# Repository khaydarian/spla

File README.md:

# SPLA: Super Nintendo PPU Logic Analyzer

The 1990-era Super Nintendo Entertainment System is a venerable gaming console,
and although its hardware is aging and hard to come by, it has long had
well-establish software emulators, preserving gaming history for generations to
come.

However, while most of the SNES hardware has been effectively
reverse-engineered by writing test programs for the CPU (sometimes taking
advantage of undocumented behavior to figure out details), one remaining
component of the console has resisted complete analysis: the "Picture
Processing Unit" chips, `PPU-1` and `PPU-2`.

The PPU chips are together responsible for managing the sprites, backgrounds,
and palettes for each frame of a game's video output, and produce the analog
scanline signal in realtime, which then appears on the
player's TV.  However, the output video signals (and video ram bus) are
entirely inaccessible to SNES CPU, thus making analysis of the exact timing
details of these chips difficult or impossible.

A very few games for the SNES (particularly *Air Strike Patrol*) use the SNES
video hardware in unexpected ways, which depend on the detailed timing of the
PPU chips during scanline rendering.  This makes accurately emulating these
games' graphics difficult -- emulator developers have to manually compare
emulator output with what the game actually shows on the screen, and try to
guess how the PPU evaluates these unusual configurations.  Without complete
understanding of the chips operation, this process degenerates into a
frustruating game of whack-a-mole.

To be confident that we have faithfully reproduced the entire SNES, we need to
characterize all the PPU outputs at the level of individual clock cycles, and
rigorously compare the behavior of a software emulator to that of the actual,
physical chips.

This project is intended to design a breakout circuit board, integrating the
SNES PPU chips from a real vintage SNES console, combined with surrounding
modern hardware, to effectively form a >100-pin-wide digital logic analyzer,
combined with single-frame analog video capture system.  With this board built,
and sufficient supporting software written, it should be possible to
experimentally characterize the entire operation of the PPU chips, thus
producing a completely cycle-accurate emulation of the SNES video hardware.

</img>

## Current Status

* Design complete.
* Schematic complete.
* PCB layout complete.
* Schematic and PCB review complete (enough).
* Lab setup essentially complete.
* Bringup started.
  * Power bringup complete.
  * USB / FTDI bringup complete.
  * FPGA bringup complete.
  * Level shifter bringup complete.
  * SNES bringup complete.
  * Analog bringup pending.
* Software development in progress.
  * Early bringup and testing software complete.
* RTL development in progress.
  * All bringup images complete.
  * Low-speed driver image in progress.
  * High-speed driver image pending.

## Design components

* The USB interface to a host PC is based on an FTDI `FT2232H` chip, which can
  drive up to 60MBps (USB 2.0 "Full Speed" maximum throughput).
* A Lattice `ECP5` FPGA, which forms the central brains of the board.
* Both SNES `PPU` chips, and their corresponding video SRAM chips (which are
  standard 32KiB 8-bit SRAM chips, but are old enough that they're hard to
  source).
* A whole bunch of 3.3V / 5V level shifter chips (`74LVC8T245`), as the SNES
  chips are 5V TTL, but almost everything modern is 3.3V at most.
* Three `ADC1173` high-speed 8-bit analog-to-digital converter chips, to
  capture the analog RGB signal output and convert it back to digital for
  analysis. This also requires a handful (5) of `LMH6611` opamps to drive the
  ADC inputs and establish reliable references.

## References

* [Original post that inspired this project](https://byuu.org/articles/edge-of-emulation)
* [Ars Technica Article](https://arstechnica.com/gaming/2020/04/how-snes-emulators-got-a-few-pixels-from-complete-perfection/)

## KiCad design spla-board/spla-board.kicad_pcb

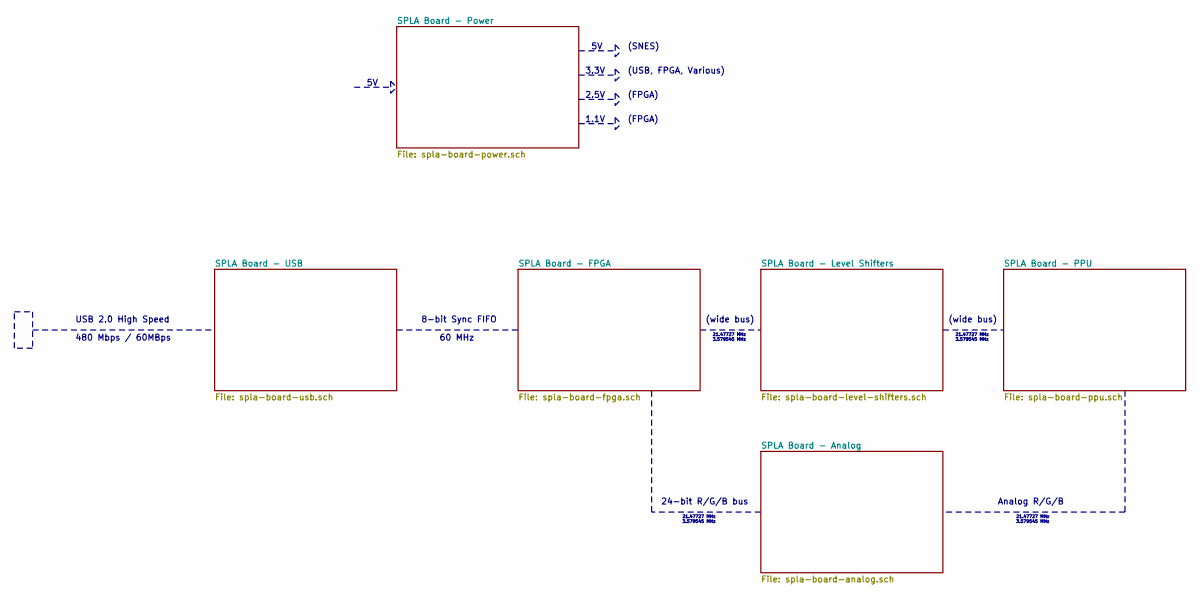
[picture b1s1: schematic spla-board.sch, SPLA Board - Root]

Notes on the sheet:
USB 2.0 High Speed
60 MHz
(wide bus)
Analog R/G/B
24-bit R/G/B bus
3.3V
2.5V
1.1V
(SNES)
(USB, FPGA, Various)
(FPGA)
8-bit Sync FIFO
21.47727 MHz 3.579545 MHz
480 Mbps / 60MBps

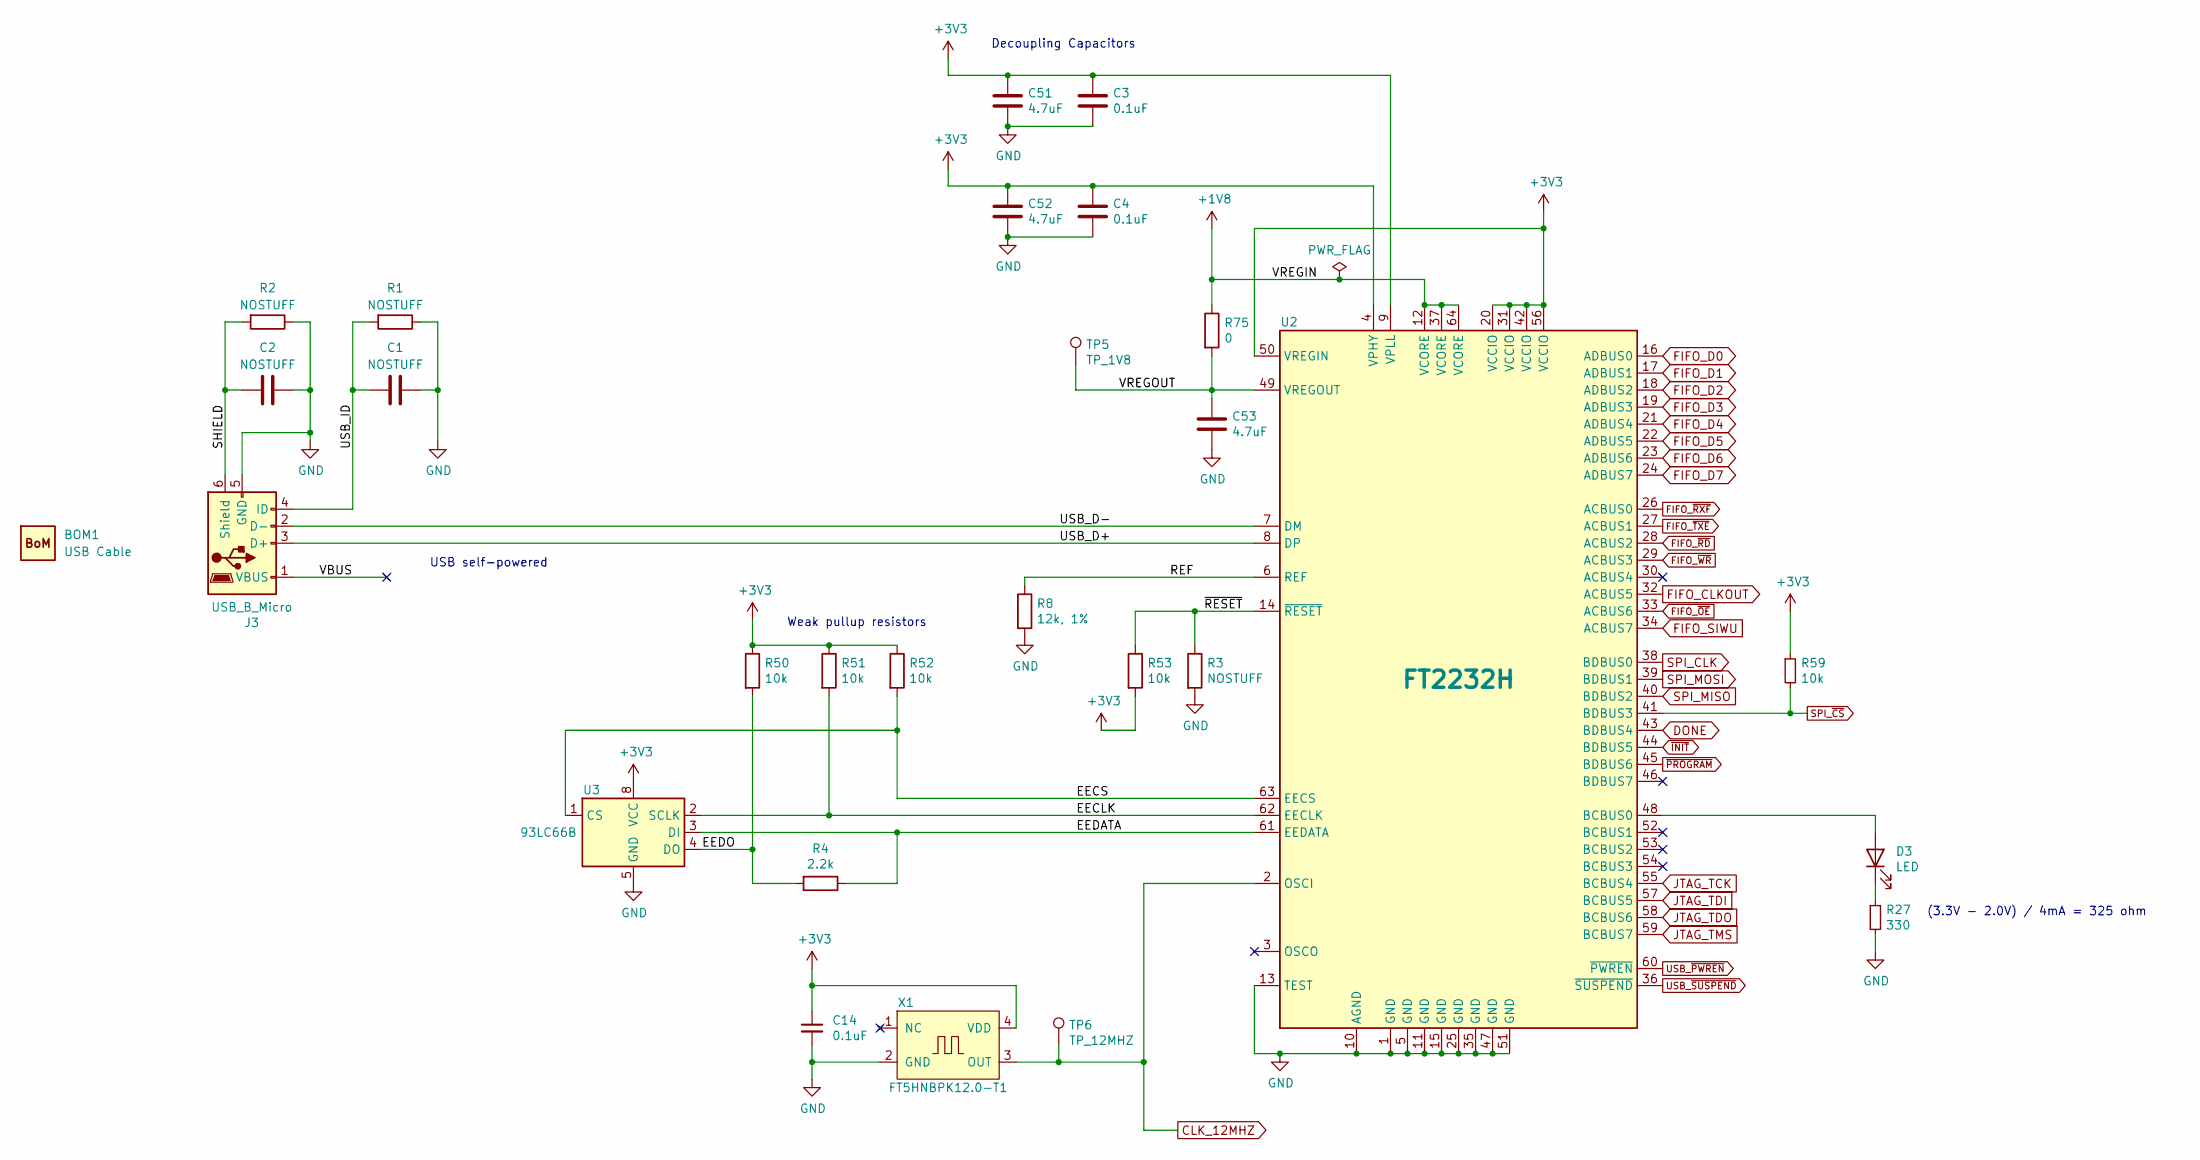
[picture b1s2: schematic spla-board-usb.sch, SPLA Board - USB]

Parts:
BOM1: USB Cable; BoM; Digikey Q966-ND
C1, C2: NOSTUFF; C_0603_1608Metric; Digikey N/A
C3, C4, C14: 0.1uF; C_0603_1608Metric; Digikey 490-16477-1-ND
C51, C52, C53: 4.7uF; C_0603_1608Metric; Digikey 490-7203-1-ND
D3: LED; LED_0805_2012Metric; Digikey 732-4986-1-ND
J3: USB_B_Micro; USB_Micro-B_Wuerth_629105150521; Digikey 732-5960-1-ND
R1, R2, R3: NOSTUFF; R_0603_1608Metric; Digikey N/A
R4: 2.2k; R_0603_1608Metric; Digikey RMCF0603JT2K20CT-ND
R8: 12k, 1%; R_0603_1608Metric; Digikey RMCF0603FT12K0CT-ND
R27: 330; R_0603_1608Metric; Digikey RMCF0603JT330RCT-ND
R50, R51, R52, R53, R59: 10k; R_0603_1608Metric; Digikey RMCF0603JT10K0CT-ND
R75: 0; R_0603_1608Metric; Digikey 2019-RK73Z1JTTDCT-ND
TP5: TP_1V8; TestPoint_Pad_D1.0mm; Digikey N/A
TP6: TP_12MHZ; TestPoint_Pad_D1.0mm; Digikey N/A
U2: FT2232H; LQFP-64_10x10mm_P0.5mm; Digikey 768-1024-1-ND
U3: 93LC66B; SOIC-8_3.9x4.9mm_P1.27mm; Digikey 93LC66B/SN-ND
X1: FT5HNBPK12.0-T1; Crystal_SMD_5032-4Pin_5.0x3.2mm; Digikey 631-1068-1-ND

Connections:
+1V8: R75.1, U2.12 (VCORE), U2.37 (VCORE), U2.64 (VCORE)
/SPLA Board - USB/EECLK: R51.2, U2.62 (EECLK), U3.2 (SCLK)
/SPLA Board - USB/EECS: R52.2, U2.63 (EECS), U3.1 (CS)
/SPLA Board - USB/EEDATA: R4.1, U2.61 (EEDATA), U3.3 (DI)
/SPLA Board - USB/EEDO: R4.2, R50.2, U3.4 (DO)
/SPLA Board - USB/REF: R8.1, U2.6 (REF)
/SPLA Board - USB/SHIELD: C2.2, J3.6 (Shield), R2.2
/SPLA Board - USB/USB_D+: J3.3 (D+), U2.8 (DP)
/SPLA Board - USB/USB_D-: J3.2 (D-), U2.7 (DM)
/SPLA Board - USB/USB_ID: C1.2, J3.4 (ID), R1.2
/SPLA Board - USB/VBUS: J3.1 (VBUS)
/SPLA Board - USB/VREGOUT: C53.1, R75.2, TP5.1, U2.49 (VREGOUT)
/SPLA Board - USB/~RESET: R3.1, R53.1, U2.14 (~RESET)
CLK_12MHZ: TP6.1, U2.2 (OSCI), X1.3 (OUT); also elsewhere on the board
DONE: U2.43 (BDBUS4); also elsewhere on the board
FIFO_CLKOUT: U2.32 (ACBUS5); also elsewhere on the board
FIFO_D0: U2.16 (ADBUS0); also elsewhere on the board
FIFO_D1: U2.17 (ADBUS1); also elsewhere on the board
FIFO_D2: U2.18 (ADBUS2); also elsewhere on the board
FIFO_D3: U2.19 (ADBUS3); also elsewhere on the board
FIFO_D4: U2.21 (ADBUS4); also elsewhere on the board
FIFO_D5: U2.22 (ADBUS5); also elsewhere on the board
FIFO_D6: U2.23 (ADBUS6); also elsewhere on the board
FIFO_D7: U2.24 (ADBUS7); also elsewhere on the board
FIFO_SIWU: U2.34 (ACBUS7); also elsewhere on the board
FIFO_~OE~: U2.33 (ACBUS6); also elsewhere on the board
FIFO_~RD~: U2.28 (ACBUS2); also elsewhere on the board
FIFO_~RXF~: U2.26 (ACBUS0); also elsewhere on the board
FIFO_~TXE~: U2.27 (ACBUS1); also elsewhere on the board
FIFO_~WR~: U2.29 (ACBUS3); also elsewhere on the board
GND: C1.1, C2.1, C3.2, C4.2, C14.2, C51.2, C52.2, C53.2, J3.5 (GND), R1.1, R2.1, R3.2, R8.2, R27.2, U2.1 (GND), U2.5 (GND), U2.10 (AGND), U2.11 (GND), U2.13 (TEST), U2.15 (GND), U2.25 (GND), U2.35 (GND), U2.47 (GND), U2.51 (GND), U3.5 (GND), X1.2 (GND); also elsewhere on the board
JTAG_TCK: U2.55 (BCBUS4); also elsewhere on the board
JTAG_TDI: U2.57 (BCBUS5); also elsewhere on the board
JTAG_TDO: U2.58 (BCBUS6); also elsewhere on the board
JTAG_TMS: U2.59 (BCBUS7); also elsewhere on the board
unnamed: D3.1 (K), R27.1
unnamed: D3.2 (A), U2.48 (BCBUS0)
SPI_CLK: U2.38 (BDBUS0); also elsewhere on the board
SPI_MISO: U2.40 (BDBUS2); also elsewhere on the board
SPI_MOSI: U2.39 (BDBUS1); also elsewhere on the board
SPI_~CS~: R59.2, U2.41 (BDBUS3); also elsewhere on the board
USB_~PWREN~: U2.60 (~PWREN); also elsewhere on the board
USB_~SUSPEND~: U2.36 (~SUSPEND); also elsewhere on the board
~INIT: U2.44 (BDBUS5); also elsewhere on the board
~PROGRAM: U2.45 (BDBUS6); also elsewhere on the board

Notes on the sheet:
Weak pullup resistors
Decoupling Capacitors
USB self-powered
(3.3V - 2.0V) / 4mA = 325 ohm

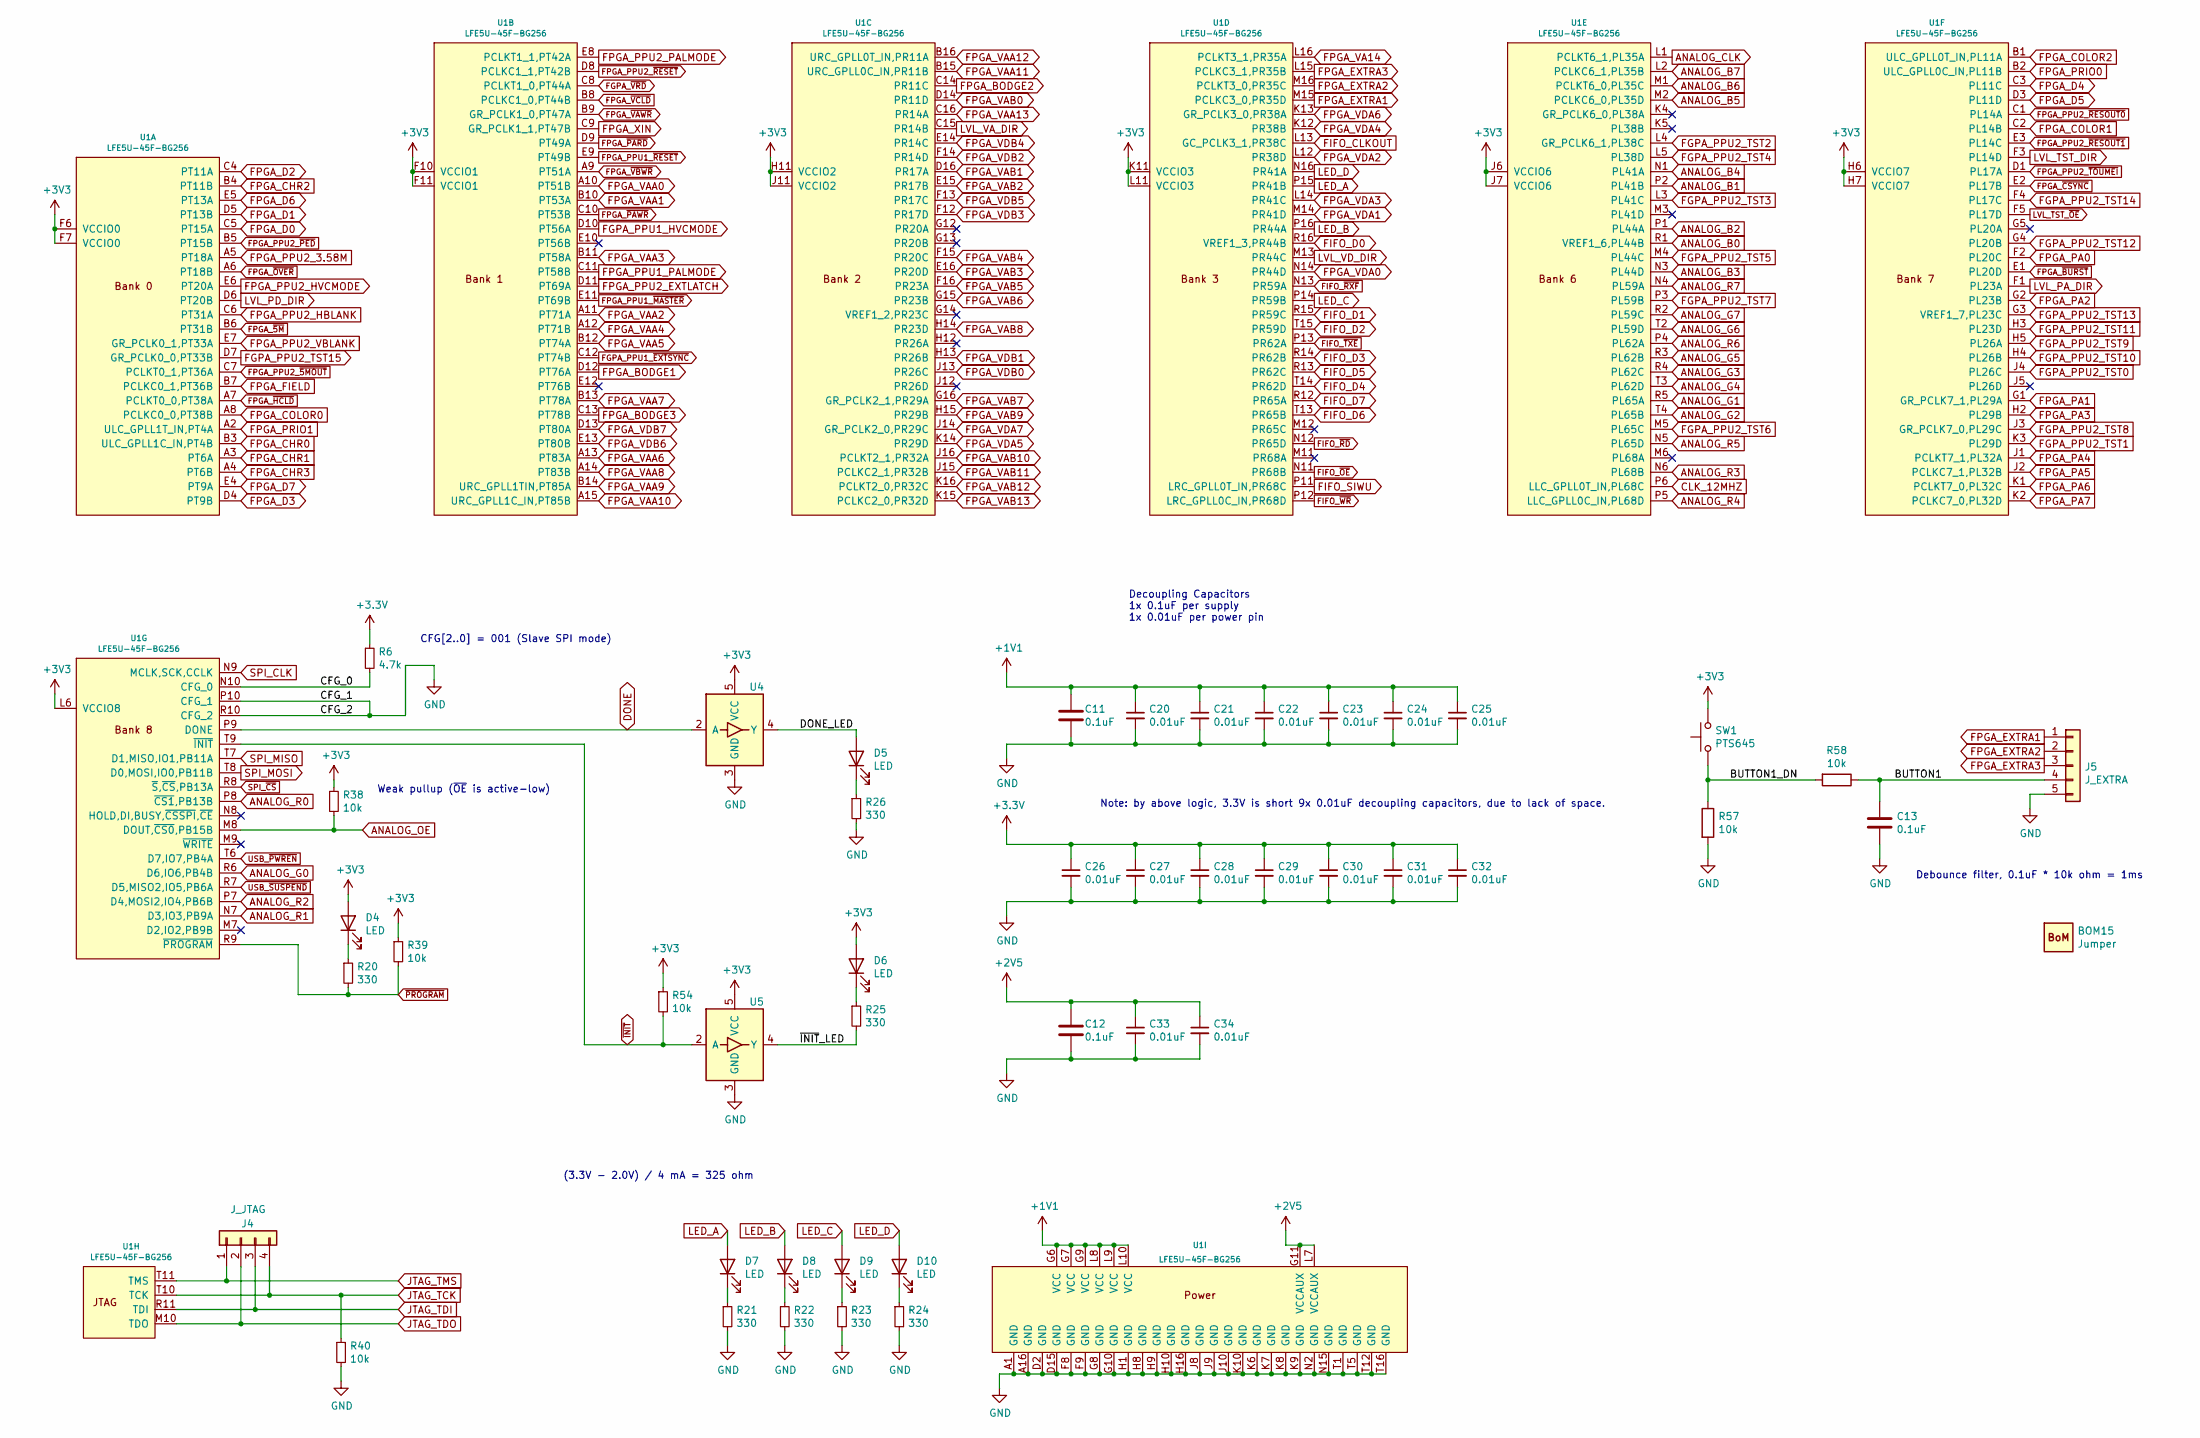
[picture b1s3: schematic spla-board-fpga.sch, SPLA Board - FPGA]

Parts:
BOM15: Jumper; BoM; Digikey S9337-ND
C11, C12, C13: 0.1uF; C_0603_1608Metric; Digikey 490-16477-1-ND
C20, C21, C22, C23, C24, C25, C26, C27, C28, C29, C30, C31, C32, C33, C34: 0.01uF; C_0402_1005Metric; Digikey 490-6351-1-ND
D4, D5, D6, D7, D8, D9, D10: LED; LED_0805_2012Metric; Digikey 732-4986-1-ND
J4: J_JTAG; PinHeader_1x04_P2.54mm_Vertical; Digikey S1011EC-40-ND
J5: J_EXTRA; PinHeader_1x05_P2.54mm_Vertical; Digikey S1011EC-40-ND
R6: 4.7k; R_0402_1005Metric; Digikey RMCF0402FT4K70CT-ND
R20, R21, R22, R23, R24, R25, R26: 330; R_0603_1608Metric; Digikey RMCF0603JT330RCT-ND
R38, R39, R40, R54, R57, R58: 10k; R_0603_1608Metric; Digikey RMCF0603JT10K0CT-ND
SW1: PTS645; PTS645-SMTR92; Digikey CKN9088CT-ND
U1: LFE5U-45F-BG256; BGA-256_14.0x14.0mm_Layout16x16_P0.8mm_Ball0.45mm_Pad0.32mm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; Digikey 220-2198-ND
U4, U5: 74LVC1G17; SOT-353_SC-70-5; Digikey 1727-4117-1-ND

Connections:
+1V1: C11.1, C20.1, C21.1, C22.1, C23.1, C24.1, C25.1, U1.G6 (VCC), U1.G7 (VCC), U1.G9 (VCC), U1.L8 (VCC), U1.L9 (VCC), U1.L10 (VCC); also elsewhere on the board
+2V5: C12.1, C33.1, C34.1, U1.G11 (VCCAUX), U1.L7 (VCCAUX); also elsewhere on the board
/SPLA Board - FPGA/BUTTON1: C13.1, J5.4, R58.1
/SPLA Board - FPGA/BUTTON1_DN: R57.1, R58.2, SW1.1
/SPLA Board - FPGA/CFG_0: R6.2, U1.N10 (CFG_0)
/SPLA Board - FPGA/DONE_LED: D5.2 (A), U4.4 (Y)
/SPLA Board - FPGA/~INIT~_LED: R25.2, U5.4 (Y)
ANALOG_B0: U1.R1 (VREF1_6,PL44B); also elsewhere on the board
ANALOG_B1: U1.P2 (PL41B); also elsewhere on the board
ANALOG_B2: U1.P1 (PL44A); also elsewhere on the board
ANALOG_B3: U1.N3 (PL44D); also elsewhere on the board
ANALOG_B4: U1.N1 (PL41A); also elsewhere on the board
ANALOG_B5: U1.M2 (PCLKC6_0,PL35D); also elsewhere on the board
ANALOG_B6: U1.M1 (PCLKT6_0,PL35C); also elsewhere on the board
ANALOG_B7: U1.L2 (PCLKC6_1,PL35B); also elsewhere on the board
ANALOG_CLK: U1.L1 (PCLKT6_1,PL35A); also elsewhere on the board
ANALOG_G0: U1.R6 (D6,IO6,PB4B); also elsewhere on the board
ANALOG_G1: U1.R5 (PL65A); also elsewhere on the board
ANALOG_G2: U1.T4 (PL65B); also elsewhere on the board
ANALOG_G3: U1.R4 (PL62C); also elsewhere on the board
ANALOG_G4: U1.T3 (PL62D); also elsewhere on the board
ANALOG_G5: U1.R3 (PL62B); also elsewhere on the board
ANALOG_G6: U1.T2 (PL59D); also elsewhere on the board
ANALOG_G7: U1.R2 (PL59C); also elsewhere on the board
ANALOG_OE: R38.2, U1.M8 (DOUT,~CS0~,PB15B); also elsewhere on the board
ANALOG_R0: U1.P8 (~CS1~,PB13B); also elsewhere on the board
ANALOG_R1: U1.N7 (D3,IO3,PB9A); also elsewhere on the board
ANALOG_R2: U1.P7 (D4,MOSI2,IO4,PB6B); also elsewhere on the board
ANALOG_R3: U1.N6 (PL68B); also elsewhere on the board
ANALOG_R4: U1.P5 (LLC_GPLL0C_IN,PL68D); also elsewhere on the board
ANALOG_R5: U1.N5 (PL65D); also elsewhere on the board
ANALOG_R6: U1.P4 (PL62A); also elsewhere on the board
ANALOG_R7: U1.N4 (PL59A); also elsewhere on the board
CLK_12MHZ: U1.P6 (LLC_GPLL0T_IN,PL68C); also elsewhere on the board
DONE: U1.P9 (DONE), U4.2 (A); also elsewhere on the board
FGPA_PPU1_HVCMODE: U1.D10 (PT56A); also elsewhere on the board
FGPA_PPU1_~EXTSYNC~: U1.C12 (PT74B); also elsewhere on the board
FGPA_PPU2_TST0: U1.J4 (PL26C); also elsewhere on the board
FGPA_PPU2_TST1: U1.K3 (PL29D); also elsewhere on the board
FGPA_PPU2_TST2: U1.L4 (GR_PCLK6_1,PL38C); also elsewhere on the board
FGPA_PPU2_TST3: U1.L3 (PL41C); also elsewhere on the board
FGPA_PPU2_TST4: U1.L5 (PL38D); also elsewhere on the board
FGPA_PPU2_TST5: U1.M4 (PL44C); also elsewhere on the board
FGPA_PPU2_TST6: U1.M5 (PL65C); also elsewhere on the board
FGPA_PPU2_TST7: U1.P3 (PL59B); also elsewhere on the board
FGPA_PPU2_TST8: U1.J3 (GR_PCLK7_0,PL29C); also elsewhere on the board
FGPA_PPU2_TST9: U1.H5 (PL26A); also elsewhere on the board
FGPA_PPU2_TST10: U1.H4 (PL26B); also elsewhere on the board
FGPA_PPU2_TST11: U1.H3 (PL23D); also elsewhere on the board
FGPA_PPU2_TST12: U1.G4 (PL20B); also elsewhere on the board
FGPA_PPU2_TST13: U1.G3 (VREF1_7,PL23C); also elsewhere on the board
FGPA_PPU2_TST14: U1.F4 (PL17C); also elsewhere on the board
FGPA_PPU2_TST15: U1.D7 (GR_PCLK0_0,PT33B); also elsewhere on the board
FGPA_~VRD~: U1.C8 (PCLKT1_0,PT44A); also elsewhere on the board
FIFO_CLKOUT: U1.L13 (GC_PCLK3_1,PR38C); also elsewhere on the board
FIFO_D0: U1.R16 (VREF1_3,PR44B); also elsewhere on the board
FIFO_D1: U1.R15 (PR59C); also elsewhere on the board
FIFO_D2: U1.T15 (PR59D); also elsewhere on the board
FIFO_D3: U1.R14 (PR62B); also elsewhere on the board
FIFO_D4: U1.T14 (PR62D); also elsewhere on the board
FIFO_D5: U1.R13 (PR62C); also elsewhere on the board
FIFO_D6: U1.T13 (PR65B); also elsewhere on the board
FIFO_D7: U1.R12 (PR65A); also elsewhere on the board
FIFO_SIWU: U1.P11 (LRC_GPLL0T_IN,PR68C); also elsewhere on the board
FIFO_~OE~: U1.N11 (PR68B); also elsewhere on the board
FIFO_~RD~: U1.N12 (PR65D); also elsewhere on the board
FIFO_~RXF~: U1.N13 (PR59A); also elsewhere on the board
FIFO_~TXE~: U1.P13 (PR62A); also elsewhere on the board
FIFO_~WR~: U1.P12 (LRC_GPLL0C_IN,PR68D); also elsewhere on the board
FPGA_BODGE1: U1.D12 (PT76A); also elsewhere on the board
FPGA_BODGE2: U1.C14 (PR11C); also elsewhere on the board
FPGA_BODGE3: U1.C13 (PT78B); also elsewhere on the board
FPGA_CHR0: U1.B3 (ULC_GPLL1C_IN,PT4B); also elsewhere on the board
FPGA_CHR1: U1.A3 (PT6A); also elsewhere on the board
FPGA_CHR2: U1.B4 (PT11B); also elsewhere on the board
FPGA_CHR3: U1.A4 (PT6B); also elsewhere on the board
FPGA_COLOR0: U1.A8 (PCLKC0_0,PT38B); also elsewhere on the board
FPGA_COLOR1: U1.C2 (PL14B); also elsewhere on the board
FPGA_COLOR2: U1.B1 (ULC_GPLL0T_IN,PL11A); also elsewhere on the board
FPGA_D0: U1.C5 (PT15A); also elsewhere on the board
FPGA_D1: U1.D5 (PT13B); also elsewhere on the board
FPGA_D2: U1.C4 (PT11A); also elsewhere on the board
FPGA_D3: U1.D4 (PT9B); also elsewhere on the board
FPGA_D4: U1.C3 (PL11C); also elsewhere on the board
FPGA_D5: U1.D3 (PL11D); also elsewhere on the board
FPGA_D6: U1.E5 (PT13A); also elsewhere on the board
FPGA_D7: U1.E4 (PT9A); also elsewhere on the board
FPGA_EXTRA1: J5.1, U1.M15 (PCLKC3_0,PR35D)
FPGA_EXTRA2: J5.2, U1.M16 (PCLKT3_0,PR35C)
FPGA_EXTRA3: J5.3, U1.L15 (PCLKC3_1,PR35B)
FPGA_FIELD: U1.B7 (PCLKC0_1,PT36B); also elsewhere on the board
FPGA_PA0: U1.F2 (PL20C); also elsewhere on the board
FPGA_PA1: U1.G1 (GR_PCLK7_1,PL29A); also elsewhere on the board
FPGA_PA2: U1.G2 (PL23B); also elsewhere on the board
FPGA_PA3: U1.H2 (PL29B); also elsewhere on the board
FPGA_PA4: U1.J1 (PCLKT7_1,PL32A); also elsewhere on the board
FPGA_PA5: U1.J2 (PCLKC7_1,PL32B); also elsewhere on the board
FPGA_PA6: U1.K1 (PCLKT7_0,PL32C); also elsewhere on the board
FPGA_PA7: U1.K2 (PCLKC7_0,PL32D); also elsewhere on the board
FPGA_PPU1_PALMODE: U1.C11 (PT58B); also elsewhere on the board
FPGA_PPU1_~MASTER~: U1.E11 (PT69B); also elsewhere on the board
FPGA_PPU1_~RESET~: U1.E9 (PT49B); also elsewhere on the board
FPGA_PPU2_3.58M: U1.A5 (PT18A); also elsewhere on the board
FPGA_PPU2_EXTLATCH: U1.D11 (PT69A); also elsewhere on the board
FPGA_PPU2_HBLANK: U1.C6 (PT31A); also elsewhere on the board
FPGA_PPU2_HVCMODE: U1.E6 (PT20A); also elsewhere on the board
FPGA_PPU2_PALMODE: U1.E8 (PCLKT1_1,PT42A); also elsewhere on the board
FPGA_PPU2_VBLANK: U1.E7 (GR_PCLK0_1,PT33A); also elsewhere on the board
FPGA_PPU2_~5MOUT~: U1.C7 (PCLKT0_1,PT36A); also elsewhere on the board
FPGA_PPU2_~PED~: U1.B5 (PT15B); also elsewhere on the board
FPGA_PPU2_~RESET~: U1.D8 (PCLKC1_1,PT42B); also elsewhere on the board
FPGA_PPU2_~RESOUT0~: U1.C1 (PL14A); also elsewhere on the board
FPGA_PPU2_~RESOUT1~: U1.E3 (PL14C); also elsewhere on the board
FPGA_PPU2_~TOUMEI~: U1.D1 (PL17A); also elsewhere on the board
FPGA_PRIO0: U1.B2 (ULC_GPLL0C_IN,PL11B); also elsewhere on the board
FPGA_PRIO1: U1.A2 (ULC_GPLL1T_IN,PT4A); also elsewhere on the board
FPGA_VA14: U1.L16 (PCLKT3_1,PR35A); also elsewhere on the board
FPGA_VAA0: U1.A10 (PT51B); also elsewhere on the board
FPGA_VAA1: U1.B10 (PT53A); also elsewhere on the board
FPGA_VAA2: U1.A11 (PT71A); also elsewhere on the board
FPGA_VAA3: U1.B11 (PT58A); also elsewhere on the board
FPGA_VAA4: U1.A12 (PT71B); also elsewhere on the board
FPGA_VAA5: U1.B12 (PT74A); also elsewhere on the board
FPGA_VAA6: U1.A13 (PT83A); also elsewhere on the board
FPGA_VAA7: U1.B13 (PT78A); also elsewhere on the board
FPGA_VAA8: U1.A14 (PT83B); also elsewhere on the board
FPGA_VAA9: U1.B14 (URC_GPLL1TIN,PT85A); also elsewhere on the board
FPGA_VAA10: U1.A15 (URC_GPLL1C_IN,PT85B); also elsewhere on the board
FPGA_VAA11: U1.B15 (URC_GPLL0C_IN,PR11B); also elsewhere on the board
FPGA_VAA12: U1.B16 (URC_GPLL0T_IN,PR11A); also elsewhere on the board
FPGA_VAA13: U1.C16 (PR14A); also elsewhere on the board
FPGA_VAB0: U1.D14 (PR11D); also elsewhere on the board
FPGA_VAB1: U1.D16 (PR17A); also elsewhere on the board
FPGA_VAB2: U1.E15 (PR17B); also elsewhere on the board
FPGA_VAB3: U1.E16 (PR20D); also elsewhere on the board
FPGA_VAB4: U1.F15 (PR20C); also elsewhere on the board
FPGA_VAB5: U1.F16 (PR23A); also elsewhere on the board
FPGA_VAB6: U1.G15 (PR23B); also elsewhere on the board
FPGA_VAB7: U1.G16 (GR_PCLK2_1,PR29A); also elsewhere on the board
FPGA_VAB8: U1.H14 (PR23D); also elsewhere on the board
FPGA_VAB9: U1.H15 (PR29B); also elsewhere on the board
FPGA_VAB10: U1.J16 (PCLKT2_1,PR32A); also elsewhere on the board
FPGA_VAB11: U1.J15 (PCLKC2_1,PR32B); also elsewhere on the board
FPGA_VAB12: U1.K16 (PCLKT2_0,PR32C); also elsewhere on the board
FPGA_VAB13: U1.K15 (PCLKC2_0,PR32D); also elsewhere on the board
FPGA_VDA0: U1.N14 (PR44D); also elsewhere on the board
FPGA_VDA1: U1.M14 (PR41D); also elsewhere on the board
FPGA_VDA2: U1.L12 (PR38D); also elsewhere on the board
FPGA_VDA3: U1.L14 (PR41C); also elsewhere on the board
FPGA_VDA4: U1.K12 (PR38B); also elsewhere on the board
FPGA_VDA5: U1.K14 (PR29D); also elsewhere on the board
FPGA_VDA6: U1.K13 (GR_PCLK3_0,PR38A); also elsewhere on the board
FPGA_VDA7: U1.J14 (GR_PCLK2_0,PR29C); also elsewhere on the board
FPGA_VDB0: U1.J13 (PR26C); also elsewhere on the board
FPGA_VDB1: U1.H13 (PR26B); also elsewhere on the board
FPGA_VDB2: U1.F14 (PR14D); also elsewhere on the board
FPGA_VDB3: U1.F12 (PR17D); also elsewhere on the board
FPGA_VDB4: U1.E14 (PR14C); also elsewhere on the board
FPGA_VDB5: U1.F13 (PR17C); also elsewhere on the board
FPGA_VDB6: U1.E13 (PT80B); also elsewhere on the board
FPGA_VDB7: U1.D13 (PT80A); also elsewhere on the board
FPGA_XIN: U1.C9 (GR_PCLK1_1,PT47B); also elsewhere on the board
FPGA_~5M~: U1.B6 (PT31B); also elsewhere on the board
FPGA_~BURST~: U1.E1 (PL20D); also elsewhere on the board
FPGA_~CSYNC~: U1.E2 (PL17B); also elsewhere on the board
FPGA_~HCLD: U1.A7 (PCLKT0_0,PT38A); also elsewhere on the board
FPGA_~OVER~: U1.A6 (PT18B); also elsewhere on the board
FPGA_~PARD~: U1.D9 (PT49A); also elsewhere on the board
FPGA_~PAWR~: U1.C10 (PT53B); also elsewhere on the board
FPGA_~VAWR~: U1.B9 (GR_PCLK1_0,PT47A); also elsewhere on the board
FPGA_~VBWR~: U1.A9 (PT51A); also elsewhere on the board
FPGA_~VCLD~: U1.B8 (PCLKC1_0,PT44B); also elsewhere on the board
GND: C11.2, C12.2, C13.2, C20.2, C21.2, C22.2, C23.2, C24.2, C25.2, C26.2, C27.2, C28.2, C29.2, C30.2, C31.2, C32.2, C33.2, C34.2, J5.5, R21.2, R22.2, R23.2, R24.2, R26.2, R40.2, R57.2, U1.A1 (GND), U1.A16 (GND), U1.D2 (GND), U1.D15 (GND), U1.F8 (GND), U1.F9 (GND), U1.G8 (GND), U1.G10 (GND), U1.H1 (GND), U1.H8 (GND), U1.H9 (GND), U1.H10 (GND), U1.H16 (GND), U1.J8 (GND), U1.J9 (GND), U1.J10 (GND), U1.K6 (GND), U1.K7 (GND), U1.K8 (GND), U1.K9 (GND), U1.K10 (GND), U1.N2 (GND), U1.N15 (GND), U1.P10 (CFG_1), U1.R10 (CFG_2), U1.T1 (GND), U1.T5 (GND), U1.T12 (GND), U1.T16 (GND), U4.3 (GND), U5.3 (GND); also elsewhere on the board
JTAG_TCK: J4.4, R40.1, U1.T10 (TCK); also elsewhere on the board
JTAG_TDI: J4.3, U1.R11 (TDI); also elsewhere on the board
JTAG_TDO: J4.2, U1.M10 (TDO); also elsewhere on the board
JTAG_TMS: J4.1, U1.T11 (TMS); also elsewhere on the board
LED_A: D7.2 (A), U1.P15 (PR41B)
LED_B: D8.2 (A), U1.P16 (PR44A)
LED_C: D9.2 (A), U1.P14 (PR59B)
LED_D: D10.2 (A), U1.N16 (PR41A)
LVL_PA_DIR: U1.F1 (PL23A); also elsewhere on the board
LVL_PD_DIR: U1.D6 (PT20B); also elsewhere on the board
LVL_TST_DIR: U1.F3 (PL14D); also elsewhere on the board
LVL_TST_~OE~: U1.F5 (PL17D); also elsewhere on the board
LVL_VA_DIR: U1.C15 (PR14B); also elsewhere on the board
LVL_VD_DIR: U1.M13 (PR44C); also elsewhere on the board
unnamed: D4.1 (K), R20.1
unnamed: D5.1 (K), R26.1
unnamed: D6.1 (K), R25.1
unnamed: D7.1 (K), R21.1
unnamed: D8.1 (K), R22.1
unnamed: D9.1 (K), R23.1
unnamed: D10.1 (K), R24.1
SPI_CLK: U1.N9 (MCLK,SCK,CCLK); also elsewhere on the board
SPI_MISO: U1.T7 (D1,MISO,IO1,PB11A); also elsewhere on the board
SPI_MOSI: U1.T8 (D0,MOSI,IO0,PB11B); also elsewhere on the board
SPI_~CS~: U1.R8 (~S~,~CS~,PB13A); also elsewhere on the board
USB_~PWREN~: U1.T6 (D7,IO7,PB4A); also elsewhere on the board
USB_~SUSPEND~: U1.R7 (D5,MISO2,IO5,PB6A); also elsewhere on the board
~INIT: R54.2, U1.T9 (~INIT), U5.2 (A); also elsewhere on the board
~PROGRAM: R20.2, R39.2, U1.R9 (~PROGRAM); also elsewhere on the board

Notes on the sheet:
CFG[2..0] = 001 (Slave SPI mode)
(3.3V - 2.0V) / 4 mA = 325 ohm
Decoupling Capacitors 1x 0.1uF per supply 1x 0.01uF per power pin
Note: by above logic, 3.3V is short 9x 0.01uF decoupling capacitors, due to lack of space.
Weak pullup (~OE~ is active-low)
Debounce filter, 0.1uF * 10k ohm = 1ms
